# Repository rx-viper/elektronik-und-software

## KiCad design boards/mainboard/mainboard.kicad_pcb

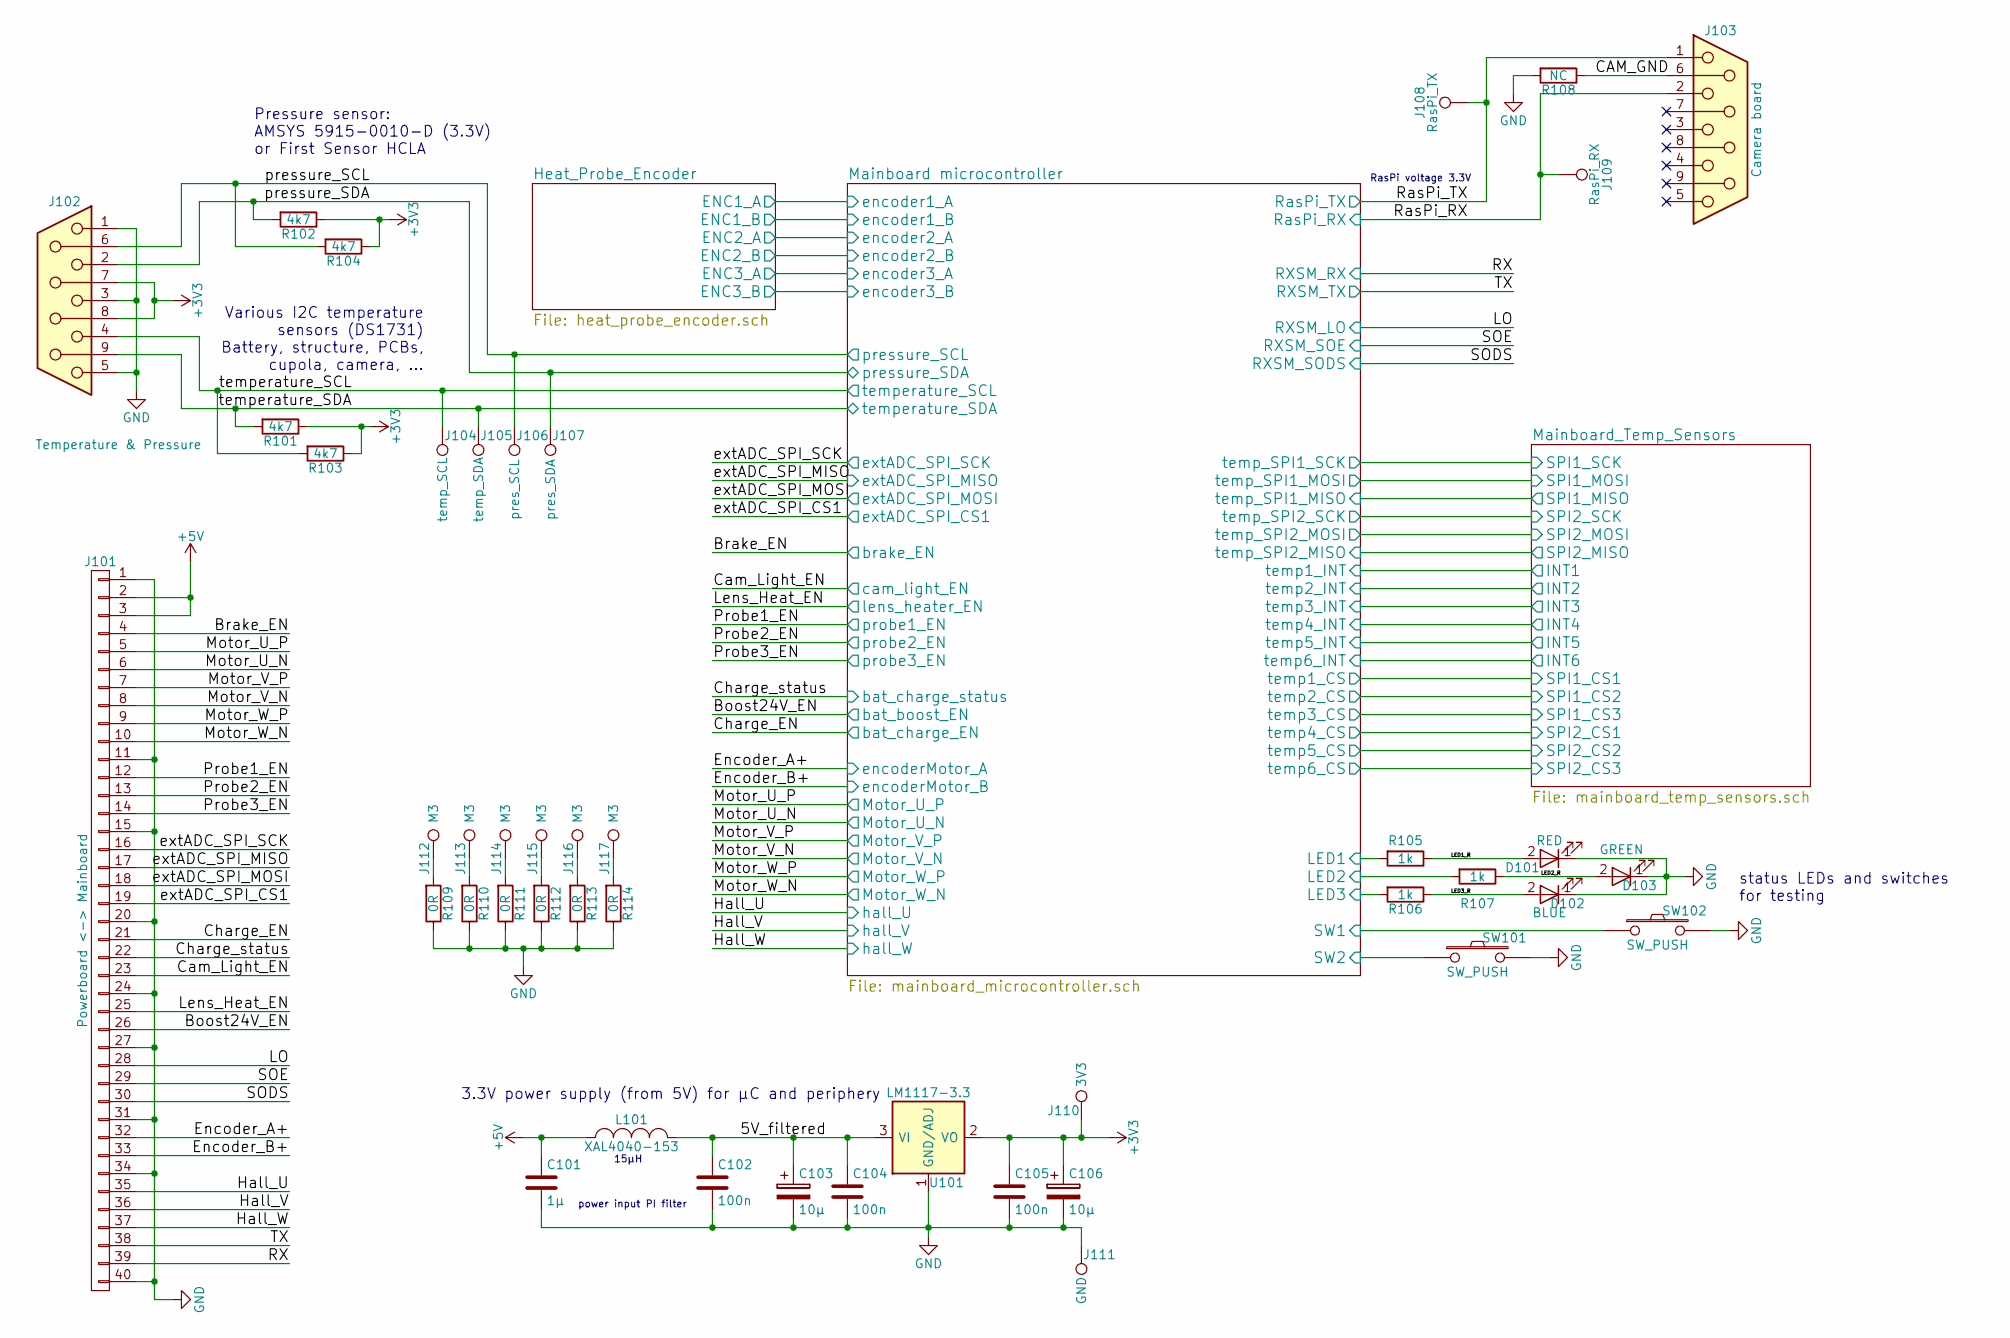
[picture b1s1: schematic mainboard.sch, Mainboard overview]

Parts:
C101: 1µ; C_0603
C102, C104, C105: 100n; C_0603
C103, C106: 10µ; C_0805
D101: RED; LED_0603
D102: BLUE; LED_0603
D103: GREEN; LED_0603
J101: Powerboard <-> Mainboard; Pin_Header_Straight_2x20_Pitch2.54mm
J102: Temperature & Pressure; DB9FD
J103: Camera board; DB9FD
J104: temp_SCL; Measurement_Point_Round-SMD-Pad_Small
J105: temp_SDA; Measurement_Point_Round-SMD-Pad_Small
J106: pres_SCL; Measurement_Point_Round-SMD-Pad_Small
J107: pres_SDA; Measurement_Point_Round-SMD-Pad_Small
J108: RasPi_TX; Measurement_Point_Round-SMD-Pad_Small
J109: RasPi_RX; Measurement_Point_Round-SMD-Pad_Small
J110: 3V3; Measurement_Point_Round-SMD-Pad_Small
J111: GND; Measurement_Point_Round-SMD-Pad_Small
J112, J113, J114, J115, J116, J117: M3; MountingHole_3.2mm_M3_Pad
L101: XAL4040-153; L_Coilcraft_XAL40xx_Handsoldering
R101, R102, R103, R104: 4k7; R_0603
R105, R106, R107: 1k; R_0603
R108: NC; R_0603
R109, R110, R111, R112, R113, R114: 0R; R_0603
SW101, SW102: SW_PUSH; SW_SPST_FSMSM
U101: LM1117-3.3; SOT-223

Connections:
+3V3: C105.1, C106.1, J102.7, J102.8, J110.1, R101.1, R102.1, R103.1, R104.1, U101.2 (VO), U101.4 (VO); also elsewhere on the board
+5V: C101.1, J101.2, J101.3, L101.1; also elsewhere on the board
/5V_filtered: C102.1, C103.1, C104.1, L101.2, U101.3 (VI)
/Boost24V_EN: J101.26; also elsewhere on the board
/Brake_EN: J101.4; also elsewhere on the board
/CAM_GND: J103.6, R108.1
/Cam_Light_EN: J101.23; also elsewhere on the board
/Charge_EN: J101.21; also elsewhere on the board
/Charge_status: J101.22; also elsewhere on the board
/Encoder_A+: J101.32; also elsewhere on the board
/Encoder_B+: J101.33; also elsewhere on the board
/Hall_U: J101.35; also elsewhere on the board
/Hall_V: J101.36; also elsewhere on the board
/Hall_W: J101.37; also elsewhere on the board
/LED1_R: D101.2 (A), R105.1
/LED2_R: D103.2 (A), R107.1
/LED3_R: D102.2 (A), R106.1
/LO: J101.28; also elsewhere on the board
/Lens_Heat_EN: J101.25; also elsewhere on the board
/Mainboard microcontroller/LED1: R105.2; also elsewhere on the board
/Mainboard microcontroller/LED2: R107.2; also elsewhere on the board
/Mainboard microcontroller/LED3: R106.2; also elsewhere on the board
/Mainboard microcontroller/SW1: SW102.1; also elsewhere on the board
/Mainboard microcontroller/SW2: SW101.1; also elsewhere on the board
/Motor_U_N: J101.6; also elsewhere on the board
/Motor_U_P: J101.5; also elsewhere on the board
/Motor_V_N: J101.8; also elsewhere on the board
/Motor_V_P: J101.7; also elsewhere on the board
/Motor_W_N: J101.10; also elsewhere on the board
/Motor_W_P: J101.9; also elsewhere on the board
/Probe1_EN: J101.12; also elsewhere on the board
/Probe2_EN: J101.13; also elsewhere on the board
/Probe3_EN: J101.14; also elsewhere on the board
/RX: J101.39; also elsewhere on the board
/RasPi_RX: J103.2, J109.1; also elsewhere on the board
/RasPi_TX: J103.1, J108.1; also elsewhere on the board
/SODS: J101.30; also elsewhere on the board
/SOE: J101.29; also elsewhere on the board
/TX: J101.38; also elsewhere on the board
/extADC_SPI_CS1: J101.19; also elsewhere on the board
/extADC_SPI_MISO: J101.17; also elsewhere on the board
/extADC_SPI_MOSI: J101.18; also elsewhere on the board
/extADC_SPI_SCK: J101.16; also elsewhere on the board
/pressure_SCL: J102.6, J106.1, R104.2; also elsewhere on the board
/pressure_SDA: J102.2, J107.1, R102.2; also elsewhere on the board
/temperature_SCL: J102.4, J104.1, R103.2; also elsewhere on the board
/temperature_SDA: J102.9, J105.1, R101.2; also elsewhere on the board
GND: C101.2, C102.2, C103.2, C104.2, C105.2, C106.2, D101.1 (K), D102.1 (K), D103.1 (K), J101.1, J101.11, J101.15, J101.20, J101.24, J101.27, J101.31, J101.34, J101.40, J102.1, J102.3, J102.5, J111.1, R108.2, R109.1, R110.1, R111.1, R112.1, R113.1, R114.1, SW101.2, SW102.2, U101.1 (GND/ADJ); also elsewhere on the board
unnamed: J112.1, R109.2
unnamed: J113.1, R110.2
unnamed: J114.1, R111.2
unnamed: J115.1, R112.2
unnamed: J116.1, R113.2
unnamed: J117.1, R114.2

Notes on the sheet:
RasPi voltage 3.3V
power input PI filter
Pressure sensor: AMSYS 5915-0010-D (3.3V) or First Sensor HCLA
Various I2C temperature sensors (DS1731) Battery, structure, PCBs, cupola, camera, ...
3.3V power supply (from 5V) for µC and periphery
status LEDs and switches for testing
15µH

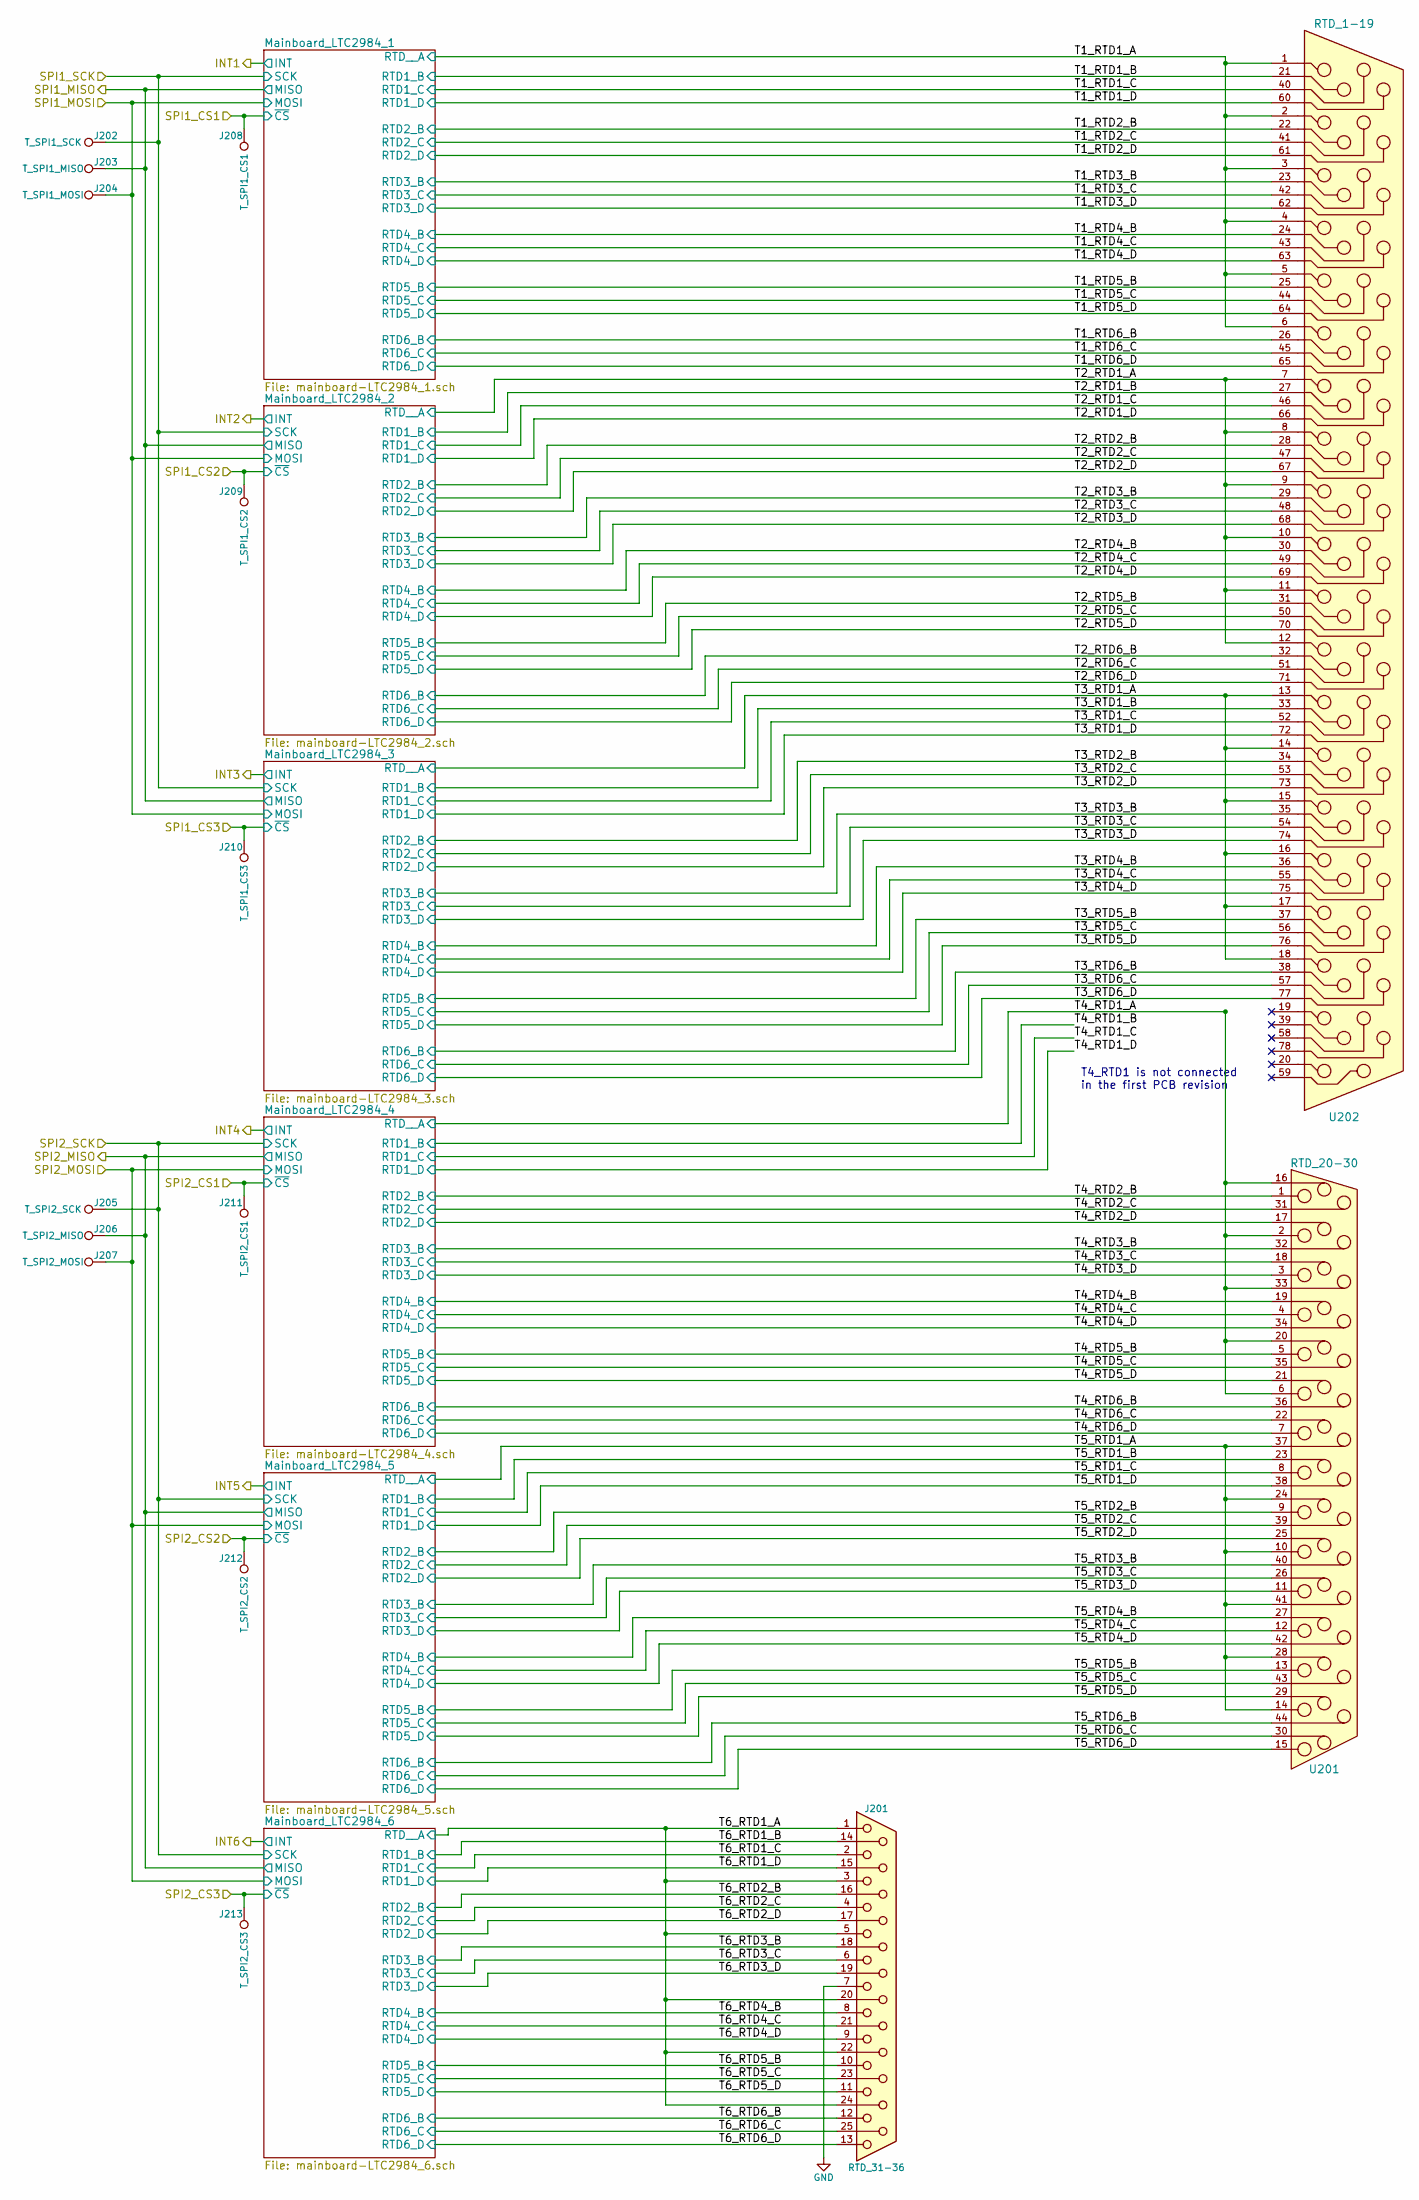
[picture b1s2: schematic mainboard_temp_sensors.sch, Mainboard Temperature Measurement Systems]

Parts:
J201: RTD_31-36; DB25FD
J202: T_SPI1_SCK; Measurement_Point_Round-SMD-Pad_Small
J203: T_SPI1_MISO; Measurement_Point_Round-SMD-Pad_Small
J204: T_SPI1_MOSI; Measurement_Point_Round-SMD-Pad_Small
J205: T_SPI2_SCK; Measurement_Point_Round-SMD-Pad_Small
J206: T_SPI2_MISO; Measurement_Point_Round-SMD-Pad_Small
J207: T_SPI2_MOSI; Measurement_Point_Round-SMD-Pad_Small
J208: T_SPI1_CS1; Measurement_Point_Round-SMD-Pad_Small
J209: T_SPI1_CS2; Measurement_Point_Round-SMD-Pad_Small
J210: T_SPI1_CS3; Measurement_Point_Round-SMD-Pad_Small
J211: T_SPI2_CS1; Measurement_Point_Round-SMD-Pad_Small
J212: T_SPI2_CS2; Measurement_Point_Round-SMD-Pad_Small
J213: T_SPI2_CS3; Measurement_Point_Round-SMD-Pad_Small
U201: RTD_20-30; D-Sub_HD_44_F
U202: RTD_1-19; D-Sub_HD_78_F

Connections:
/Mainboard_Temp_Sensors/SPI1_CS1: J208.1; also elsewhere on the board
/Mainboard_Temp_Sensors/SPI1_CS2: J209.1; also elsewhere on the board
/Mainboard_Temp_Sensors/SPI1_CS3: J210.1; also elsewhere on the board
/Mainboard_Temp_Sensors/SPI1_MISO: J203.1; also elsewhere on the board
/Mainboard_Temp_Sensors/SPI1_MOSI: J204.1; also elsewhere on the board
/Mainboard_Temp_Sensors/SPI1_SCK: J202.1; also elsewhere on the board
/Mainboard_Temp_Sensors/SPI2_CS1: J211.1; also elsewhere on the board
/Mainboard_Temp_Sensors/SPI2_CS2: J212.1; also elsewhere on the board
/Mainboard_Temp_Sensors/SPI2_CS3: J213.1; also elsewhere on the board
/Mainboard_Temp_Sensors/SPI2_MISO: J206.1; also elsewhere on the board
/Mainboard_Temp_Sensors/SPI2_MOSI: J207.1; also elsewhere on the board
/Mainboard_Temp_Sensors/SPI2_SCK: J205.1; also elsewhere on the board
/Mainboard_Temp_Sensors/T1_RTD1_A: U202.1, U202.2, U202.3, U202.4, U202.5, U202.6; also elsewhere on the board
/Mainboard_Temp_Sensors/T1_RTD1_B: U202.21; also elsewhere on the board
/Mainboard_Temp_Sensors/T1_RTD1_C: U202.40; also elsewhere on the board
/Mainboard_Temp_Sensors/T1_RTD1_D: U202.60; also elsewhere on the board
/Mainboard_Temp_Sensors/T1_RTD2_B: U202.22; also elsewhere on the board
/Mainboard_Temp_Sensors/T1_RTD2_C: U202.41; also elsewhere on the board
/Mainboard_Temp_Sensors/T1_RTD2_D: U202.61; also elsewhere on the board
/Mainboard_Temp_Sensors/T1_RTD3_B: U202.23; also elsewhere on the board
/Mainboard_Temp_Sensors/T1_RTD3_C: U202.42; also elsewhere on the board
/Mainboard_Temp_Sensors/T1_RTD3_D: U202.62; also elsewhere on the board
/Mainboard_Temp_Sensors/T1_RTD4_B: U202.24; also elsewhere on the board
/Mainboard_Temp_Sensors/T1_RTD4_C: U202.43; also elsewhere on the board
/Mainboard_Temp_Sensors/T1_RTD4_D: U202.63; also elsewhere on the board
/Mainboard_Temp_Sensors/T1_RTD5_B: U202.25; also elsewhere on the board
/Mainboard_Temp_Sensors/T1_RTD5_C: U202.44; also elsewhere on the board
/Mainboard_Temp_Sensors/T1_RTD5_D: U202.64; also elsewhere on the board
/Mainboard_Temp_Sensors/T1_RTD6_B: U202.26; also elsewhere on the board
/Mainboard_Temp_Sensors/T1_RTD6_C: U202.45; also elsewhere on the board
/Mainboard_Temp_Sensors/T1_RTD6_D: U202.65; also elsewhere on the board
/Mainboard_Temp_Sensors/T2_RTD1_A: U202.7, U202.8, U202.9, U202.10, U202.11, U202.12; also elsewhere on the board
/Mainboard_Temp_Sensors/T2_RTD1_B: U202.27; also elsewhere on the board
/Mainboard_Temp_Sensors/T2_RTD1_C: U202.46; also elsewhere on the board
/Mainboard_Temp_Sensors/T2_RTD1_D: U202.66; also elsewhere on the board
/Mainboard_Temp_Sensors/T2_RTD2_B: U202.28; also elsewhere on the board
/Mainboard_Temp_Sensors/T2_RTD2_C: U202.47; also elsewhere on the board
/Mainboard_Temp_Sensors/T2_RTD2_D: U202.67; also elsewhere on the board
/Mainboard_Temp_Sensors/T2_RTD3_B: U202.29; also elsewhere on the board
/Mainboard_Temp_Sensors/T2_RTD3_C: U202.48; also elsewhere on the board
/Mainboard_Temp_Sensors/T2_RTD3_D: U202.68; also elsewhere on the board
/Mainboard_Temp_Sensors/T2_RTD4_B: U202.30; also elsewhere on the board
/Mainboard_Temp_Sensors/T2_RTD4_C: U202.49; also elsewhere on the board
/Mainboard_Temp_Sensors/T2_RTD4_D: U202.69; also elsewhere on the board
/Mainboard_Temp_Sensors/T2_RTD5_B: U202.31; also elsewhere on the board
/Mainboard_Temp_Sensors/T2_RTD5_C: U202.50; also elsewhere on the board
/Mainboard_Temp_Sensors/T2_RTD5_D: U202.70; also elsewhere on the board
/Mainboard_Temp_Sensors/T2_RTD6_B: U202.32; also elsewhere on the board
/Mainboard_Temp_Sensors/T2_RTD6_C: U202.51; also elsewhere on the board
/Mainboard_Temp_Sensors/T2_RTD6_D: U202.71; also elsewhere on the board
/Mainboard_Temp_Sensors/T3_RTD1_A: U202.13, U202.14, U202.15, U202.16, U202.17, U202.18; also elsewhere on the board
/Mainboard_Temp_Sensors/T3_RTD1_B: U202.33; also elsewhere on the board
/Mainboard_Temp_Sensors/T3_RTD1_C: U202.52; also elsewhere on the board
/Mainboard_Temp_Sensors/T3_RTD1_D: U202.72; also elsewhere on the board
/Mainboard_Temp_Sensors/T3_RTD2_B: U202.34; also elsewhere on the board
/Mainboard_Temp_Sensors/T3_RTD2_C: U202.53; also elsewhere on the board
/Mainboard_Temp_Sensors/T3_RTD2_D: U202.73; also elsewhere on the board
/Mainboard_Temp_Sensors/T3_RTD3_B: U202.35; also elsewhere on the board
/Mainboard_Temp_Sensors/T3_RTD3_C: U202.54; also elsewhere on the board
/Mainboard_Temp_Sensors/T3_RTD3_D: U202.74; also elsewhere on the board
/Mainboard_Temp_Sensors/T3_RTD4_B: U202.36; also elsewhere on the board
/Mainboard_Temp_Sensors/T3_RTD4_C: U202.55; also elsewhere on the board
/Mainboard_Temp_Sensors/T3_RTD4_D: U202.75; also elsewhere on the board
/Mainboard_Temp_Sensors/T3_RTD5_B: U202.37; also elsewhere on the board
/Mainboard_Temp_Sensors/T3_RTD5_C: U202.56; also elsewhere on the board
/Mainboard_Temp_Sensors/T3_RTD5_D: U202.76; also elsewhere on the board
/Mainboard_Temp_Sensors/T3_RTD6_B: U202.38; also elsewhere on the board
/Mainboard_Temp_Sensors/T3_RTD6_C: U202.57; also elsewhere on the board
/Mainboard_Temp_Sensors/T3_RTD6_D: U202.77; also elsewhere on the board
/Mainboard_Temp_Sensors/T4_RTD1_A: U201.2, U201.6, U201.16, U201.20, U201.33; also elsewhere on the board
/Mainboard_Temp_Sensors/T4_RTD2_B: U201.1; also elsewhere on the board
/Mainboard_Temp_Sensors/T4_RTD2_C: U201.31; also elsewhere on the board
/Mainboard_Temp_Sensors/T4_RTD2_D: U201.17; also elsewhere on the board
/Mainboard_Temp_Sensors/T4_RTD3_B: U201.32; also elsewhere on the board
/Mainboard_Temp_Sensors/T4_RTD3_C: U201.18; also elsewhere on the board
/Mainboard_Temp_Sensors/T4_RTD3_D: U201.3; also elsewhere on the board
/Mainboard_Temp_Sensors/T4_RTD4_B: U201.19; also elsewhere on the board
/Mainboard_Temp_Sensors/T4_RTD4_C: U201.4; also elsewhere on the board
/Mainboard_Temp_Sensors/T4_RTD4_D: U201.34; also elsewhere on the board
/Mainboard_Temp_Sensors/T4_RTD5_B: U201.5; also elsewhere on the board
/Mainboard_Temp_Sensors/T4_RTD5_C: U201.35; also elsewhere on the board
/Mainboard_Temp_Sensors/T4_RTD5_D: U201.21; also elsewhere on the board
/Mainboard_Temp_Sensors/T4_RTD6_B: U201.36; also elsewhere on the board
/Mainboard_Temp_Sensors/T4_RTD6_C: U201.22; also elsewhere on the board
/Mainboard_Temp_Sensors/T4_RTD6_D: U201.7; also elsewhere on the board
/Mainboard_Temp_Sensors/T5_RTD1_A: U201.10, U201.14, U201.24, U201.28, U201.37, U201.41; also elsewhere on the board
/Mainboard_Temp_Sensors/T5_RTD1_B: U201.23; also elsewhere on the board
/Mainboard_Temp_Sensors/T5_RTD1_C: U201.8; also elsewhere on the board
/Mainboard_Temp_Sensors/T5_RTD1_D: U201.38; also elsewhere on the board
/Mainboard_Temp_Sensors/T5_RTD2_B: U201.9; also elsewhere on the board
/Mainboard_Temp_Sensors/T5_RTD2_C: U201.39; also elsewhere on the board
/Mainboard_Temp_Sensors/T5_RTD2_D: U201.25; also elsewhere on the board
/Mainboard_Temp_Sensors/T5_RTD3_B: U201.40; also elsewhere on the board
/Mainboard_Temp_Sensors/T5_RTD3_C: U201.26; also elsewhere on the board
/Mainboard_Temp_Sensors/T5_RTD3_D: U201.11; also elsewhere on the board
/Mainboard_Temp_Sensors/T5_RTD4_B: U201.27; also elsewhere on the board
/Mainboard_Temp_Sensors/T5_RTD4_C: U201.12; also elsewhere on the board
/Mainboard_Temp_Sensors/T5_RTD4_D: U201.42; also elsewhere on the board
/Mainboard_Temp_Sensors/T5_RTD5_B: U201.13; also elsewhere on the board
/Mainboard_Temp_Sensors/T5_RTD5_C: U201.43; also elsewhere on the board
/Mainboard_Temp_Sensors/T5_RTD5_D: U201.29; also elsewhere on the board
/Mainboard_Temp_Sensors/T5_RTD6_B: U201.44; also elsewhere on the board
/Mainboard_Temp_Sensors/T5_RTD6_C: U201.30; also elsewhere on the board
/Mainboard_Temp_Sensors/T5_RTD6_D: U201.15; also elsewhere on the board
/Mainboard_Temp_Sensors/T6_RTD1_A: J201.1, J201.3, J201.5, J201.20, J201.22, J201.24; also elsewhere on the board
/Mainboard_Temp_Sensors/T6_RTD1_B: J201.14; also elsewhere on the board
/Mainboard_Temp_Sensors/T6_RTD1_C: J201.2; also elsewhere on the board
/Mainboard_Temp_Sensors/T6_RTD1_D: J201.15; also elsewhere on the board
/Mainboard_Temp_Sensors/T6_RTD2_B: J201.16; also elsewhere on the board
/Mainboard_Temp_Sensors/T6_RTD2_C: J201.4; also elsewhere on the board
/Mainboard_Temp_Sensors/T6_RTD2_D: J201.17; also elsewhere on the board
/Mainboard_Temp_Sensors/T6_RTD3_B: J201.18; also elsewhere on the board
/Mainboard_Temp_Sensors/T6_RTD3_C: J201.6; also elsewhere on the board
/Mainboard_Temp_Sensors/T6_RTD3_D: J201.19; also elsewhere on the board
/Mainboard_Temp_Sensors/T6_RTD4_B: J201.8; also elsewhere on the board
/Mainboard_Temp_Sensors/T6_RTD4_C: J201.21; also elsewhere on the board
/Mainboard_Temp_Sensors/T6_RTD4_D: J201.9; also elsewhere on the board
/Mainboard_Temp_Sensors/T6_RTD5_B: J201.10; also elsewhere on the board
/Mainboard_Temp_Sensors/T6_RTD5_C: J201.23; also elsewhere on the board
/Mainboard_Temp_Sensors/T6_RTD5_D: J201.11; also elsewhere on the board
/Mainboard_Temp_Sensors/T6_RTD6_B: J201.12; also elsewhere on the board
/Mainboard_Temp_Sensors/T6_RTD6_C: J201.25; also elsewhere on the board
/Mainboard_Temp_Sensors/T6_RTD6_D: J201.13; also elsewhere on the board
GND: J201.7; also elsewhere on the board

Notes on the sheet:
T4_RTD1 is not connected in the first PCB revision

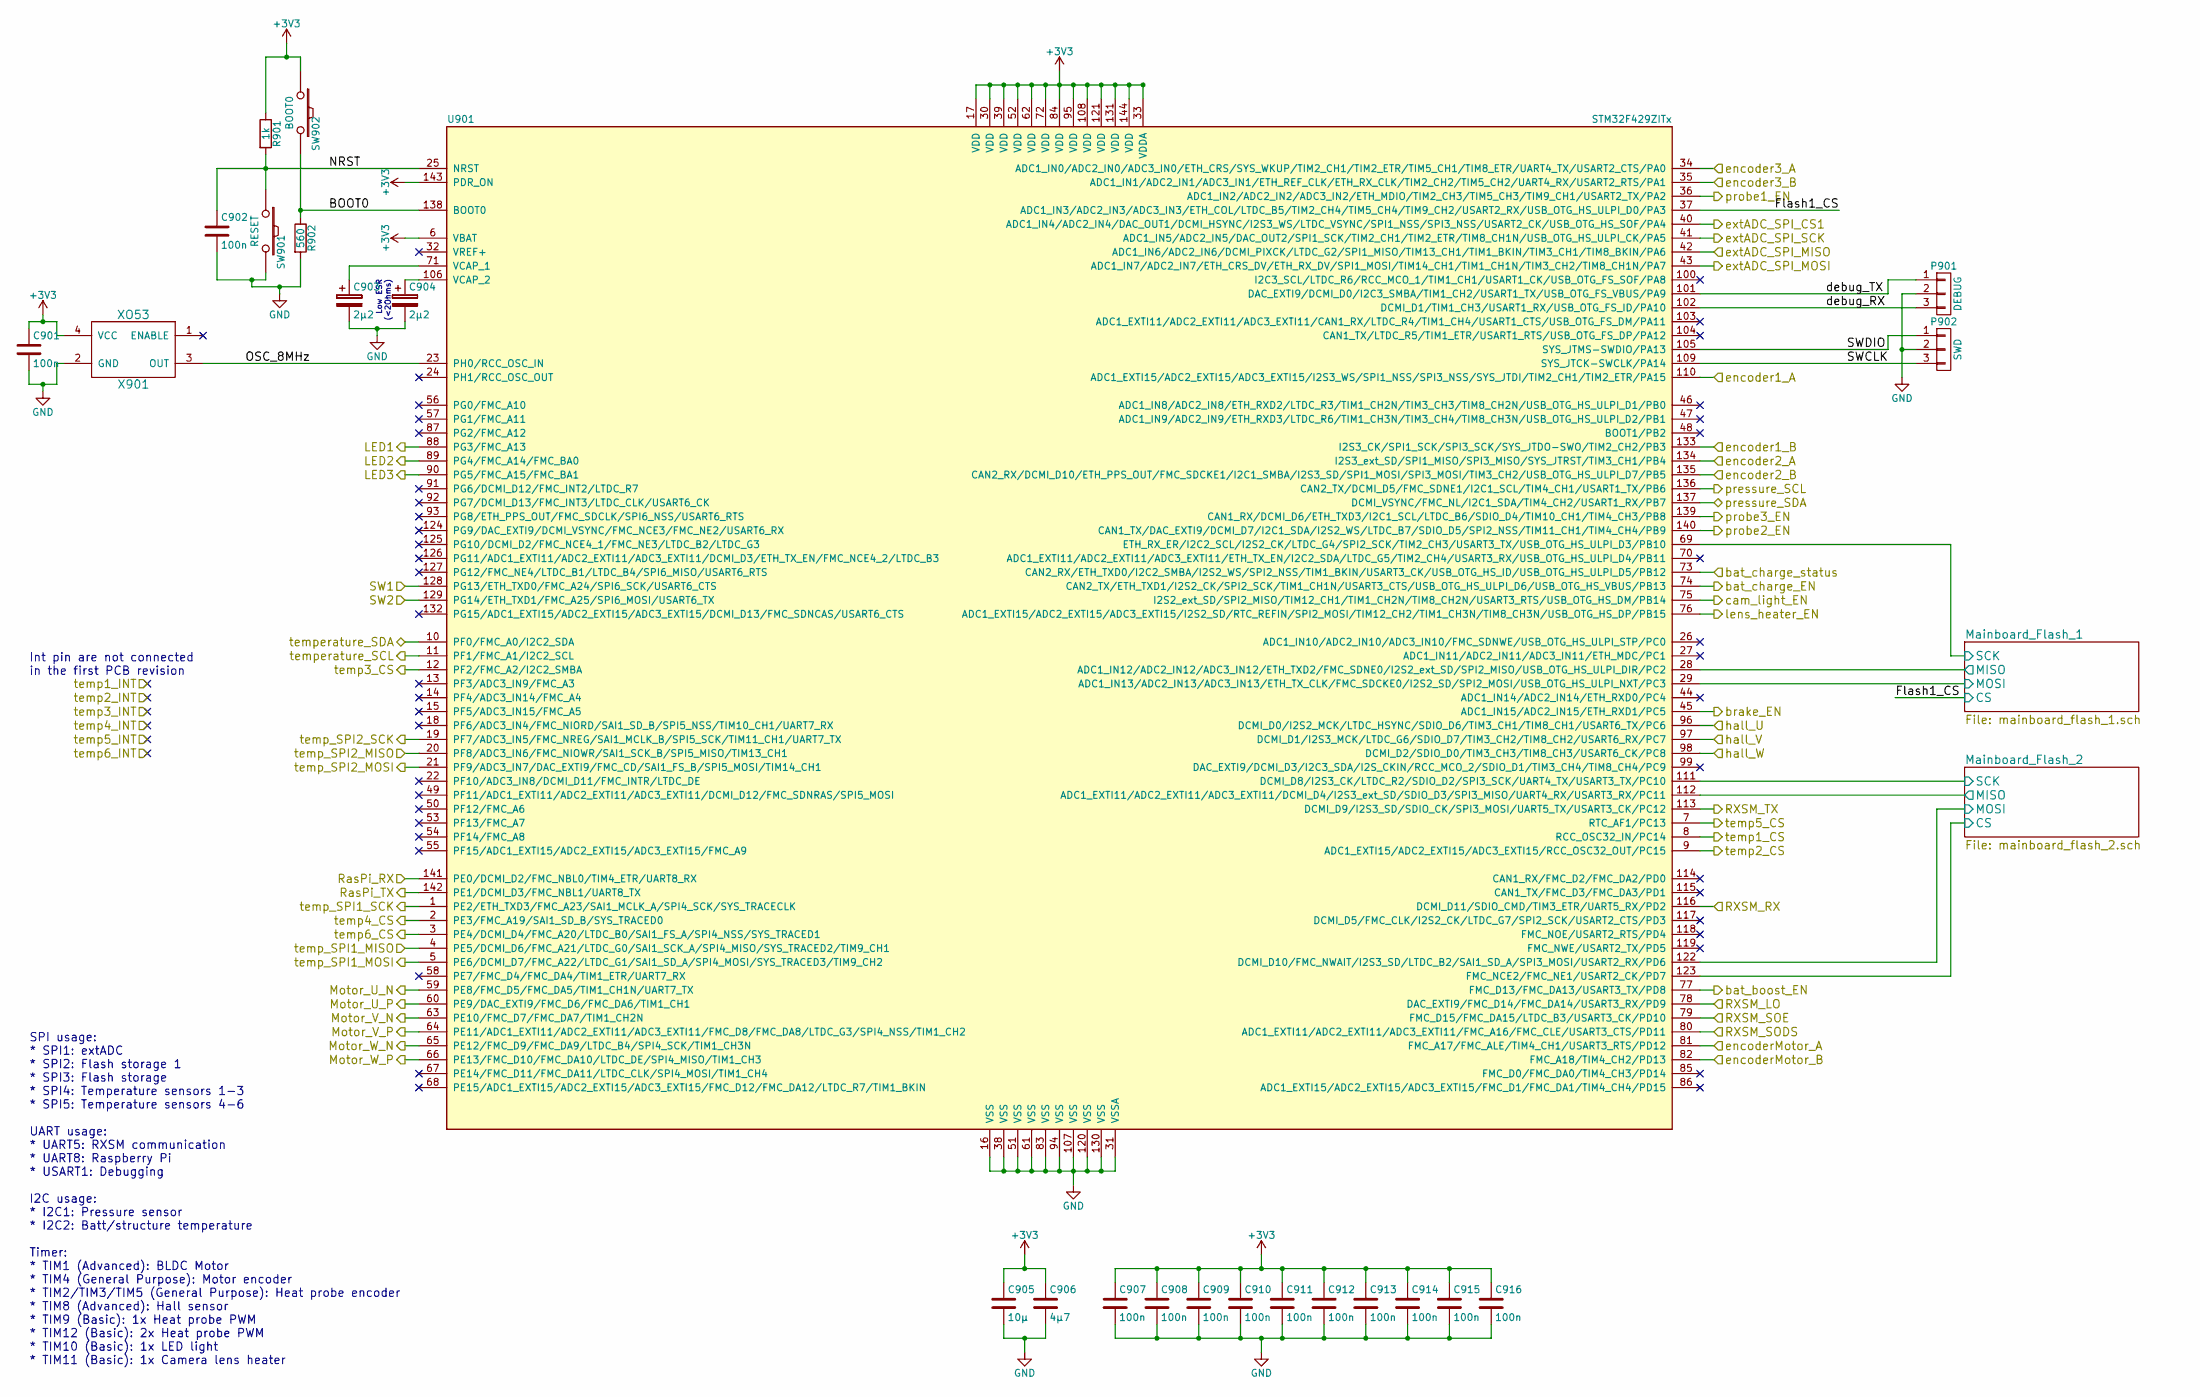
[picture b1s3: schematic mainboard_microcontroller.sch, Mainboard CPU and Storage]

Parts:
C901, C902, C907, C908, C909, C910, C911, C912, C913, C914, C915, C916: 100n; C_0603
C903, C904: 2µ2; C_0805
C905: 10µ; C_0805
C906: 4µ7; C_0805
P901: DEBUG; Pin_Header_Straight_1x03_Pitch2.54mm
P902: SWD; Pin_Header_Straight_1x03_Pitch2.54mm
R901: 1k; R_0603
R902: 560; R_0603
SW901: RESET; SW_SPST_FSMSM
SW902: BOOT0; SW_SPST_FSMSM
U901: STM32F429ZITx; TQFP-144_20x20mm_Pitch0.5mm
X901: XO53

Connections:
+3V3: C901.1, C905.1, C906.1, C907.1, C908.1, C909.1, C910.1, C911.1, C912.1, C913.1, C914.1, C915.1, C916.1, R901.1, SW902.1, U901.6 (VBAT), U901.17 (VDD), U901.30 (VDD), U901.33 (VDDA), U901.39 (VDD), U901.52 (VDD), U901.62 (VDD), U901.72 (VDD), U901.84 (VDD), U901.95 (VDD), U901.108 (VDD), U901.121 (VDD), U901.131 (VDD), U901.143 (PDR_ON), U901.144 (VDD), X901.4 (VCC); also elsewhere on the board
/Boost24V_EN: U901.77 (FMC_D13/FMC_DA13/USART3_TX/PD8); also elsewhere on the board
/Brake_EN: U901.45 (ADC1_IN15/ADC2_IN15/ETH_RXD1/PC5); also elsewhere on the board
/Cam_Light_EN: U901.75 (I2S2_ext_SD/SPI2_MISO/TIM12_CH1/TIM1_CH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); also elsewhere on the board
/Charge_EN: U901.74 (CAN2_TX/ETH_TXD1/I2S2_CK/SPI2_SCK/TIM1_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); also elsewhere on the board
/Charge_status: U901.73 (CAN2_RX/ETH_TXD0/I2C2_SMBA/I2S2_WS/SPI2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); also elsewhere on the board
/Encoder_A+: U901.81 (FMC_A17/FMC_ALE/TIM4_CH1/USART3_RTS/PD12); also elsewhere on the board
/Encoder_B+: U901.82 (FMC_A18/TIM4_CH2/PD13); also elsewhere on the board
/Hall_U: U901.96 (DCMI_D0/I2S2_MCK/LTDC_HSYNC/SDIO_D6/TIM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); also elsewhere on the board
/Hall_V: U901.97 (DCMI_D1/I2S3_MCK/LTDC_G6/SDIO_D7/TIM3_C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); also elsewhere on the board
/Hall_W: U901.98 (DCMI_D2/SDIO_D0/TIM3_CH3/TIM8_CH3/USART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); also elsewhere on the board
/Heat_Probe_Encoder/ENC1_A: U901.110 (ADC1_EXTI15/ADC2_EXTI15/ADC3_EXTI15/I2S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); also elsewhere on the board
/Heat_Probe_Encoder/ENC1_B: U901.133 (I2S3_CK/SPI1_SCK/SPI3_SCK/SYS_JTDO-SWO/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); also elsewhere on the board
/Heat_Probe_Encoder/ENC2_A: U901.134 (I2S3_ext_SD/SPI1_MISO/SPI3_MISO/SYS_JTR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); also elsewhere on the board
/Heat_Probe_Encoder/ENC2_B: U901.135 (CAN2_RX/DCMI_D10/ETH_PPS_OUT/FMC_SDCKE1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); also elsewhere on the board
/Heat_Probe_Encoder/ENC3_A: U901.34 (ADC1_IN0/ADC2_IN0/ADC3_IN0/ETH_CRS/SYS_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); also elsewhere on the board
/Heat_Probe_Encoder/ENC3_B: U901.35 (ADC1_IN1/ADC2_IN1/ADC3_IN1/ETH_REF_CLK/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); also elsewhere on the board
/LO: U901.78 (DAC_EXTI9/FMC_D14/FMC_DA14/USART3_RX/PD9); also elsewhere on the board
/Lens_Heat_EN: U901.76 (ADC1_EXTI15/ADC2_EXTI15/ADC3_EXTI15/I2S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); also elsewhere on the board
/Mainboard microcontroller/BOOT0: R902.1, SW902.2, U901.138 (BOOT0)
/Mainboard microcontroller/Flash1_CS: U901.37 (ADC1_IN3/ADC2_IN3/ADC3_IN3/ETH_COL/LTDC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); also elsewhere on the board
/Mainboard microcontroller/LED1: U901.88 (PG3/FMC_A13); also elsewhere on the board
/Mainboard microcontroller/LED2: U901.89 (PG4/FMC_A14/FMC_BA0); also elsewhere on the board
/Mainboard microcontroller/LED3: U901.90 (PG5/FMC_A15/FMC_BA1); also elsewhere on the board
/Mainboard microcontroller/Mainboard_Flash_1/MISO: U901.28 (ADC1_IN12/ADC2_IN12/ADC3_IN12/ETH_TXD2/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); also elsewhere on the board
/Mainboard microcontroller/Mainboard_Flash_1/MOSI: U901.29 (ADC1_IN13/ADC2_IN13/ADC3_IN13/ETH_TX_CL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); also elsewhere on the board
/Mainboard microcontroller/Mainboard_Flash_1/SCK: U901.69 (ETH_RX_ER/I2C2_SCL/I2S2_CK/LTDC_G4/SPI2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); also elsewhere on the board
/Mainboard microcontroller/Mainboard_Flash_2/CS: U901.123 (FMC_NCE2/FMC_NE1/USART2_CK/PD7); also elsewhere on the board
/Mainboard microcontroller/Mainboard_Flash_2/MISO: U901.112 (ADC1_EXTI11/ADC2_EXTI11/ADC3_EXTI11/DCM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); also elsewhere on the board
/Mainboard microcontroller/Mainboard_Flash_2/MOSI: U901.122 (DCMI_D10/FMC_NWAIT/I2S3_SD/LTDC_B2/SAI1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); also elsewhere on the board
/Mainboard microcontroller/Mainboard_Flash_2/SCK: U901.111 (DCMI_D8/I2S3_CK/LTDC_R2/SDIO_D2/SPI3_SC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); also elsewhere on the board
/Mainboard microcontroller/NRST: C902.1, R901.2, SW901.1, U901.25 (NRST)
/Mainboard microcontroller/OSC_8MHz: U901.23 (PH0/RCC_OSC_IN), X901.3 (OUT)
/Mainboard microcontroller/SW1: U901.128 (PG13/ETH_TXD0/FMC_A24/SPI6_SCK/USART6_C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); also elsewhere on the board
/Mainboard microcontroller/SW2: U901.129 (PG14/ETH_TXD1/FMC_A25/SPI6_MOSI/USART6_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); also elsewhere on the board
/Mainboard microcontroller/SWCLK: P902.3, U901.109 (SYS_JTCK-SWCLK/PA14)
/Mainboard microcontroller/SWDIO: P902.1, U901.105 (SYS_JTMS-SWDIO/PA13)
/Mainboard microcontroller/debug_RX: P901.3, U901.102 (DCMI_D1/TIM1_CH3/USART1_RX/USB_OTG_FS_I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)
/Mainboard microcontroller/debug_TX: P901.1, U901.101 (DAC_EXTI9/DCMI_D0/I2C3_SMBA/TIM1_CH2/US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)
/Mainboard_Temp_Sensors/SPI1_CS1: U901.8 (RCC_OSC32_IN/PC14); also elsewhere on the board
/Mainboard_Temp_Sensors/SPI1_CS2: U901.9 (ADC1_EXTI15/ADC2_EXTI15/ADC3_EXTI15/RCC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); also elsewhere on the board
/Mainboard_Temp_Sensors/SPI1_CS3: U901.12 (PF2/FMC_A2/I2C2_SMBA); also elsewhere on the board
/Mainboard_Temp_Sensors/SPI1_MISO: U901.4 (PE5/DCMI_D6/FMC_A21/LTDC_G0/SAI1_SCK_A/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); also elsewhere on the board
/Mainboard_Temp_Sensors/SPI1_MOSI: U901.5 (PE6/DCMI_D7/FMC_A22/LTDC_G1/SAI1_SD_A/S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); also elsewhere on the board
/Mainboard_Temp_Sensors/SPI1_SCK: U901.1 (PE2/ETH_TXD3/FMC_A23/SAI1_MCLK_A/SPI4_S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); also elsewhere on the board
/Mainboard_Temp_Sensors/SPI2_CS1: U901.2 (PE3/FMC_A19/SAI1_SD_B/SYS_TRACED0); also elsewhere on the board
/Mainboard_Temp_Sensors/SPI2_CS2: U901.7 (RTC_AF1/PC13); also elsewhere on the board
/Mainboard_Temp_Sensors/SPI2_CS3: U901.3 (PE4/DCMI_D4/FMC_A20/LTDC_B0/SAI1_FS_A/S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); also elsewhere on the board
/Mainboard_Temp_Sensors/SPI2_MISO: U901.20 (PF8/ADC3_IN6/FMC_NIOWR/SAI1_SCK_B/SPI5_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); also elsewhere on the board
/Mainboard_Temp_Sensors/SPI2_MOSI: U901.21 (PF9/ADC3_IN7/DAC_EXTI9/FMC_CD/SAI1_FS_B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); also elsewhere on the board
/Mainboard_Temp_Sensors/SPI2_SCK: U901.19 (PF7/ADC3_IN5/FMC_NREG/SAI1_MCLK_B/SPI5_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); also elsewhere on the board
/Motor_U_N: U901.59 (PE8/FMC_D5/FMC_DA5/TIM1_CH1N/UART7_TX); also elsewhere on the board
/Motor_U_P: U901.60 (PE9/DAC_EXTI9/FMC_D6/FMC_DA6/TIM1_CH1); also elsewhere on the board
/Motor_V_N: U901.63 (PE10/FMC_D7/FMC_DA7/TIM1_CH2N); also elsewhere on the board
/Motor_V_P: U901.64 (PE11/ADC1_EXTI11/ADC2_EXTI11/ADC3_EXTI1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); also elsewhere on the board
/Motor_W_N: U901.65 (PE12/FMC_D9/FMC_DA9/LTDC_B4/SPI4_SCK/TI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); also elsewhere on the board
/Motor_W_P: U901.66 (PE13/FMC_D10/FMC_DA10/LTDC_DE/SPI4_MISO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); also elsewhere on the board
/Probe1_EN: U901.36 (ADC1_IN2/ADC2_IN2/ADC3_IN2/ETH_MDIO/TIM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); also elsewhere on the board
/Probe2_EN: U901.140 (CAN1_TX/DAC_EXTI9/DCMI_D7/I2C1_SDA/I2S2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); also elsewhere on the board
/Probe3_EN: U901.139 (CAN1_RX/DCMI_D6/ETH_TXD3/I2C1_SCL/LTDC_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); also elsewhere on the board
/RX: U901.116 (DCMI_D11/SDIO_CMD/TIM3_ETR/UART5_RX/PD2); also elsewhere on the board
/RasPi_RX: U901.141 (PE0/DCMI_D2/FMC_NBL0/TIM4_ETR/UART8_RX); also elsewhere on the board
/RasPi_TX: U901.142 (PE1/DCMI_D3/FMC_NBL1/UART8_TX); also elsewhere on the board
/SODS: U901.80 (ADC1_EXTI11/ADC2_EXTI11/ADC3_EXTI11/FMC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); also elsewhere on the board
/SOE: U901.79 (FMC_D15/FMC_DA15/LTDC_B3/USART3_CK/PD10); also elsewhere on the board
/TX: U901.113 (DCMI_D9/I2S3_SD/SDIO_CK/SPI3_MOSI/UART5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); also elsewhere on the board
/extADC_SPI_CS1: U901.40 (ADC1_IN4/ADC2_IN4/DAC_OUT1/DCMI_HSYNC/I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); also elsewhere on the board
/extADC_SPI_MISO: U901.42 (ADC1_IN6/ADC2_IN6/DCMI_PIXCK/LTDC_G2/SP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); also elsewhere on the board
/extADC_SPI_MOSI: U901.43 (ADC1_IN7/ADC2_IN7/ETH_CRS_DV/ETH_RX_DV/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); also elsewhere on the board
/extADC_SPI_SCK: U901.41 (ADC1_IN5/ADC2_IN5/DAC_OUT2/SPI1_SCK/TIM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); also elsewhere on the board
/pressure_SCL: U901.136 (CAN2_TX/DCMI_D5/FMC_SDNE1/I2C1_SCL/TIM4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); also elsewhere on the board
/pressure_SDA: U901.137 (DCMI_VSYNC/FMC_NL/I2C1_SDA/TIM4_CH2/USA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); also elsewhere on the board
/temperature_SCL: U901.11 (PF1/FMC_A1/I2C2_SCL); also elsewhere on the board
/temperature_SDA: U901.10 (PF0/FMC_A0/I2C2_SDA); also elsewhere on the board
GND: C901.2, C902.2, C903.2, C904.2, C905.2, C906.2, C907.2, C908.2, C909.2, C910.2, C911.2, C912.2, C913.2, C914.2, C915.2, C916.2, P901.2, P902.2, R902.2, SW901.2, U901.16 (VSS), U901.31 (VSSA), U901.38 (VSS), U901.51 (VSS), U901.61 (VSS), U901.83 (VSS), U901.94 (VSS), U901.107 (VSS), U901.120 (VSS), U901.130 (VSS), X901.2 (GND); also elsewhere on the board
unnamed: C903.1, U901.71 (VCAP_1)
unnamed: C904.1, U901.106 (VCAP_2)

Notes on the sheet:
Low ESR (<2Ohms)
SPI usage: * SPI1: extADC * SPI2: Flash storage 1 * SPI3: Flash storage * SPI4: Temperature sensors 1-3 * SPI5: Temperature sensors 4-6 UART usage: * UART5: RXSM communication * UART8: Raspberry Pi * USART1: Debugging I2C usage: * I2C1: Pressure sensor * I2C2: Batt/structure temperature Timer: * TI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
Int pin are not connected in the first PCB revision

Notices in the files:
boards/mainboard/mainboard.kicad_pcb:
© Raphael Lehmann
© Raphael
boards/optical-distance/optical-distance.kicad_pcb:
©rchojetzki
boards/pi-board/pi-board.kicad_pcb:
© Leonard Rapp
boards/temperature-sensor/temerature-sensor-DS1731.kicad_pcb:
© Richard
